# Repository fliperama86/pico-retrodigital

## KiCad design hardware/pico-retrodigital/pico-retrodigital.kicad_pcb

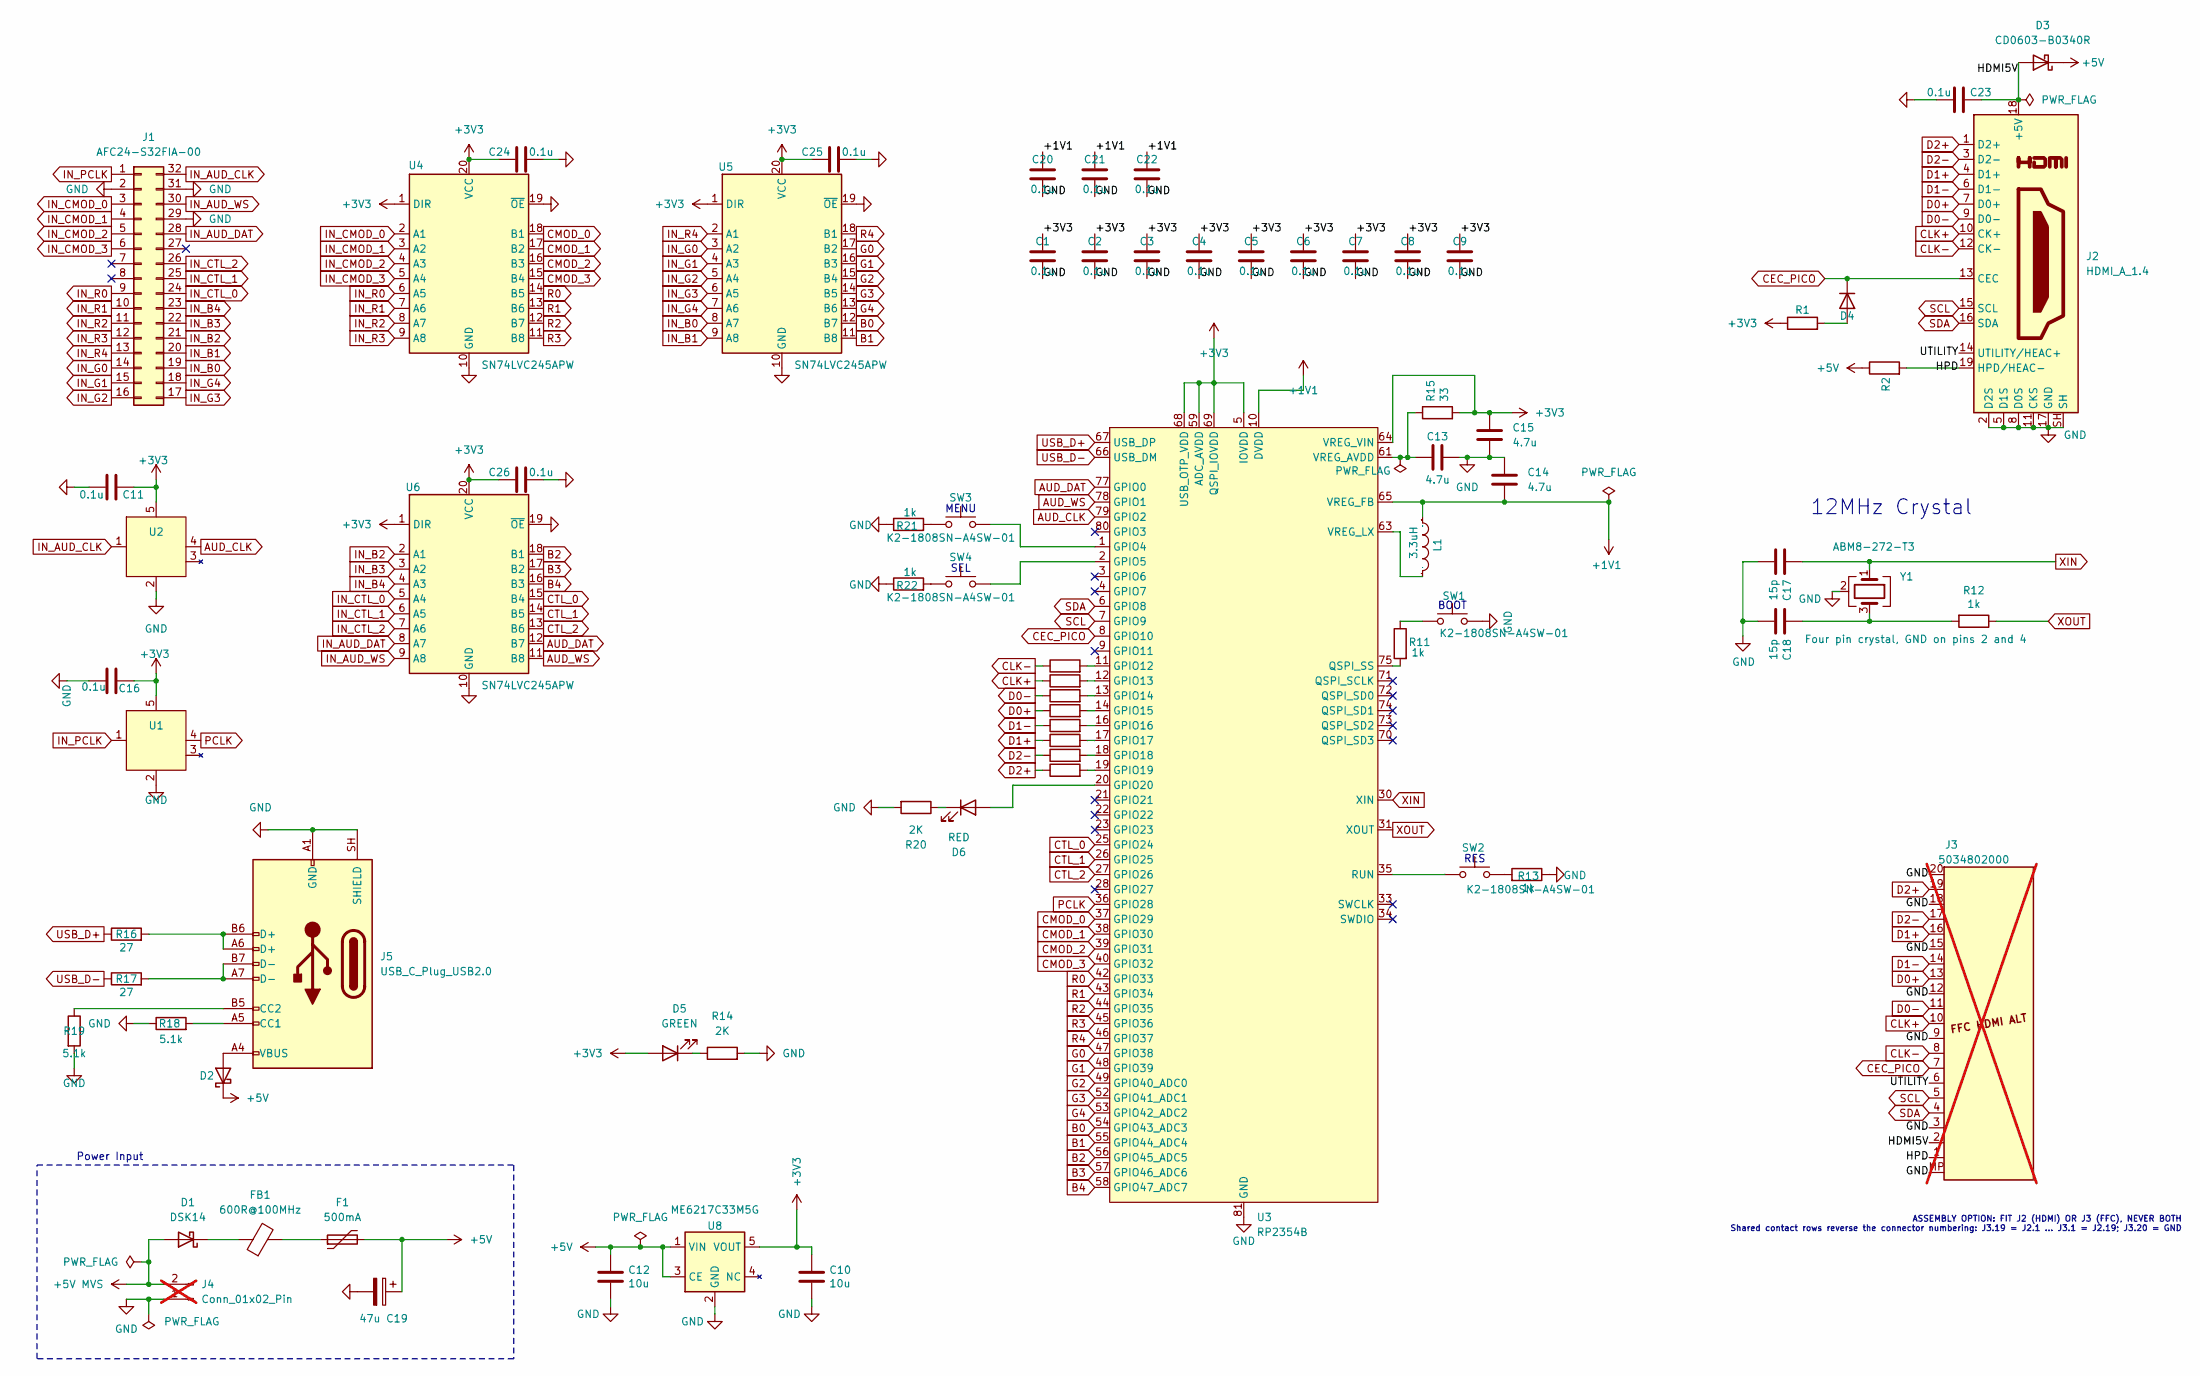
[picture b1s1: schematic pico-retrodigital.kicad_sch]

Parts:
C1, C3, C4, C5, C6, C7, C8, C9, C11, C16, C20, C21, C22, C23, C24, C25, C26: 0.1u; C_0402_1005Metric; LCSC C1525
C2: 0.1u; C_0603_1608Metric; LCSC C14663
C10, C12: 10u; C_0402_1005Metric; LCSC C15525
C13, C15: 4.7u; C_0402_1005Metric; LCSC C23733
C14: 4.7u; C_0603_1608Metric; LCSC C19666
C17, C18: 15p; C_0402_1005Metric; LCSC C1548
C19: 47u; C_1206_3216Metric; MPN CL31A476MPHNNNE; LCSC C96123
D1: DSK14; D_SOD-123; LCSC C7502711
D2: DSK14; D_SOD-123; MPN DSK14; LCSC C7502711
D3, D4: CD0603-B0340R; D_0603_1608Metric; MPN CD0603-B0340R; LCSC C3759853
D5: GREEN; LED_0603_1608Metric; MPN KT-0603YG; LCSC C2289
D6: RED; LED_0603_1608Metric; MPN KT-0603R; LCSC C2286
F1: 500mA; C_0603_1608Metric; MPN BSMD0603-050-6V; LCSC C883095
FB1: 600R@100MHz; C_0603_1608Metric; MPN BLM18KG601SN1D; LCSC C85833
J1: AFC24-S32FIA-00; FPC-SMD_P0.50-32P_JS_AFC24-S32FIA-00; MPN AFC24-S32FIA-00; LCSC C2908587
J2: HDMI_A_1.4; HDMI_A_Molex_208658-1001_Horizontal; MPN HDMI-001 19PCBTP; LCSC C138388
J3: 5034802000; FPC-SMD_5034802000; MPN 5034802000; LCSC C234192; not fitted
J4: Conn_01x02_Pin; JST_XA_B02B-XASK-1_1x02_P2.50mm_Vertical; MPN B02B-XASK-1(LF)(SN); LCSC C263753; not fitted
J5: USB_C_Plug_USB2.0; USB_C_Receptacle_HRO_TYPE-C-31-M-12; MPN TYPE-C-31-M-12; LCSC C165948
L1: IND-SMD_L2.0-W1.6_AOTA-B201610S3R3-101-T; Manufacturer Part AOTA-B201610S3R3-101-T; LCSC Part Name AOTA-B201610S3R3-101-T
R1: 27K; R_0402_1005Metric; LCSC C25771
R2: 10K; R_0603_1608Metric; LCSC C25804
R3, R4, R5, R6, R7, R8, R9, R10: 220; R_0402_1005Metric; LCSC C25091
R11, R12, R13, R21, R22: 1k; R_0402_1005Metric; LCSC C11702
R14, R20: 2K; R_0402_1005Metric; LCSC C4109
R15: 33; R_0402_1005Metric; LCSC C25105
R16, R17: 27; R_0603_1608Metric; LCSC C25190
R18, R19: 5.1k; R_0603_1608Metric; LCSC C23186
SW1, SW2, SW3, SW4: K2-1808SN-A4SW-01; SW_Push_1P1T_NO_Vertical_Wuerth_434133025816; LCSC C92589
U1, U2: SN74LVC1G17DBVR; SOT-23-5; LCSC C7836
U3: RP2354B; QFN-80-1EP_10x10mm_P0.4mm_EP3.4x3.4mm_ThermalVias; LCSC C39843328
U4, U5, U6: SN74LVC245APW; TSSOP-20_4.4x6.5mm_P0.65mm; LCSC C7848
U8: ME6217C33M5G; SOT-23-5; LCSC C427602
Y1: ABM8-272-T3; Crystal_SMD_3225-4Pin_3.2x2.5mm; LCSC C20625731

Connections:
+1V1: C14.2, C20.1, C21.1, C22.1, L1.1, U3.10 (DVDD), U3.32 (DVDD), U3.51 (DVDD), U3.65 (VREG_FB)
+3V3: C1.1, C2.1, C3.1, C4.1, C5.1, C6.1, C7.1, C8.1, C9.1, C10.1, C11.1, C15.1, C16.1, C24.1, C25.1, C26.1, D5.2 (A), R1.1, R15.2, U1.5 (VCC), U2.5 (VCC), U3.5 (IOVDD), U3.15 (IOVDD), U3.24 (IOVDD), U3.29 (IOVDD), U3.41 (IOVDD), U3.50 (IOVDD), U3.59 (ADC_AVDD), U3.60 (IOVDD), U3.64 (VREG_VIN), U3.68 (USB_OTP_VDD), U3.69 (QSPI_IOVDD), U3.76 (IOVDD), U4.1 (DIR), U4.20 (VCC), U5.1 (DIR), U5.20 (VCC), U6.1 (DIR), U6.20 (VCC), U8.5 (VOUT)
+5V: C12.1, C19.1, D2.1 (K), D3.1 (K), F1.2, R2.1, U8.1 (VIN), U8.3 (CE)
+5V MVS: D1.2 (A), J4.2
/HDMI5V: C23.1, D3.2 (A), J2.18 (+5V), J3.2 (+5V)
/HPD: J2.19 (HPD/HEAC-), J3.1 (HPD), R2.2
/UTILITY: J2.14 (UTILITY/HEAC+), J3.6 (UTILITY)
AUD_CLK: U2.4 (Y), U3.79 (GPIO2)
AUD_DAT: U3.77 (GPIO0), U6.12 (B7)
AUD_WS: U3.78 (GPIO1), U6.11 (B8)
B0: U3.54 (GPIO43_ADC3), U5.12 (B7)
B1: U3.55 (GPIO44_ADC4), U5.11 (B8)
B2: U3.56 (GPIO45_ADC5), U6.18 (B1)
B3: U3.57 (GPIO46_ADC6), U6.17 (B2)
B4: U3.58 (GPIO47_ADC7), U6.16 (B3)
CEC_PICO: D4.1 (K), J2.13 (CEC), J3.7 (CEC), U3.8 (GPIO10)
CLK+: J2.10 (CK+), J3.10 (CLK+), R5.1
CLK-: J2.12 (CK-), J3.8 (CLK-), R4.1
CMOD_0: U3.37 (GPIO29), U4.18 (B1)
CMOD_1: U3.38 (GPIO30), U4.17 (B2)
CMOD_2: U3.39 (GPIO31), U4.16 (B3)
CMOD_3: U3.40 (GPIO32), U4.15 (B4)
CTL_0: U3.25 (GPIO24), U6.15 (B4)
CTL_1: U3.26 (GPIO25), U6.14 (B5)
CTL_2: U3.27 (GPIO26), U6.13 (B6)
D0+: J2.7 (D0+), J3.13 (D0+), R6.1
D0-: J2.9 (D0-), J3.11 (D0-), R3.1
D1+: J2.4 (D1+), J3.16 (D1+), R8.1
D1-: J2.6 (D1-), J3.14 (D1-), R7.1
D2+: J2.1 (D2+), J3.19 (D2+), R10.1
D2-: J2.3 (D2-), J3.17 (D2-), R9.1
G0: U3.47 (GPIO38), U5.17 (B2)
G1: U3.48 (GPIO39), U5.16 (B3)
G2: U3.49 (GPIO40_ADC0), U5.15 (B4)
G3: U3.52 (GPIO41_ADC1), U5.14 (B5)
G4: U3.53 (GPIO42_ADC2), U5.13 (B6)
GND: C1.2, C2.2, C3.2, C4.2, C5.2, C6.2, C7.2, C8.2, C9.2, C10.2, C11.2, C12.2, C13.2, C14.1, C15.2, C16.2, C17.2, C18.2, C19.2, C20.2, C21.2, C22.2, C23.2, C24.2, C25.2, C26.2, J1.2, J1.29, J1.31, J2.2 (D2S), J2.5 (D1S), J2.8 (D0S), J2.11 (CKS), J2.17 (GND), J2.SH, J3.3 (GND), J3.9 (GND), J3.12 (GND), J3.15 (GND), J3.18 (GND), J3.20 (GND), J3.MP (SHIELD), J4.1, J5.A1 (GND), J5.A12 (GND), J5.B1 (GND), J5.B12 (GND), J5.SH (SHIELD), R13.1, R14.2, R18.1, R19.2, R20.2, R21.1, R22.1, SW1.1, U1.2 (GND), U2.2 (GND), U3.62 (VREG_PGND), U3.81 (GND), U4.10 (GND), U4.19 (~OE), U5.10 (GND), U5.19 (~OE), U6.10 (GND), U6.19 (~OE), U8.2 (GND), Y1.2 (G), Y1.4 (G)
IN_AUD_CLK: J1.32, U2.1 (A)
IN_AUD_DAT: J1.28, U6.8 (A7)
IN_AUD_WS: J1.30, U6.9 (A8)
IN_B0: J1.19, U5.8 (A7)
IN_B1: J1.20, U5.9 (A8)
IN_B2: J1.21, U6.2 (A1)
IN_B3: J1.22, U6.3 (A2)
IN_B4: J1.23, U6.4 (A3)
IN_CMOD_0: J1.3, U4.2 (A1)
IN_CMOD_1: J1.4, U4.3 (A2)
IN_CMOD_2: J1.5, U4.4 (A3)
IN_CMOD_3: J1.6, U4.5 (A4)
IN_CTL_0: J1.24, U6.5 (A4)
IN_CTL_1: J1.25, U6.6 (A5)
IN_CTL_2: J1.26, U6.7 (A6)
IN_G0: J1.14, U5.3 (A2)
IN_G1: J1.15, U5.4 (A3)
IN_G2: J1.16, U5.5 (A4)
IN_G3: J1.17, U5.6 (A5)
IN_G4: J1.18, U5.7 (A6)
IN_PCLK: J1.1, U1.1 (A)
IN_R0: J1.9, U4.6 (A5)
IN_R1: J1.10, U4.7 (A6)
IN_R2: J1.11, U4.8 (A7)
IN_R3: J1.12, U4.9 (A8)
IN_R4: J1.13, U5.2 (A1)
unnamed: C18.1, R12.2, Y1.3
unnamed: D1.1 (K), FB1.1
unnamed: D2.2 (A), J5.A4 (VBUS), J5.A9 (VBUS), J5.B4 (VBUS), J5.B9 (VBUS)
unnamed: D4.2 (A), R1.2
unnamed: D5.1 (K), R14.1
unnamed: D6.2 (A), U3.20 (GPIO20)
unnamed: D6.1 (K), R20.1
unnamed: F1.1, FB1.2
unnamed: J5.A5 (CC1), R18.2
unnamed: J5.B5 (CC2), R19.1
unnamed: J5.A6 (D+), J5.B6 (D+), R16.2
unnamed: J5.A7 (D-), J5.B7 (D-), R17.2
unnamed: R11.1, SW1.2
unnamed: R13.2, SW2.1
unnamed: R21.2, SW3.1
unnamed: R22.2, SW4.1
unnamed: SW3.2, U3.1 (GPIO4)
unnamed: SW4.2, U3.2 (GPIO5)
unnamed: R4.2, U3.11 (GPIO12)
unnamed: R5.2, U3.12 (GPIO13)
unnamed: R3.2, U3.13 (GPIO14)
unnamed: R6.2, U3.14 (GPIO15)
unnamed: R7.2, U3.16 (GPIO16)
unnamed: R8.2, U3.17 (GPIO17)
unnamed: R9.2, U3.18 (GPIO18)
unnamed: R10.2, U3.19 (GPIO19)
unnamed: R11.2, U3.75 (QSPI_SS)
unnamed: SW2.2, U3.35 (RUN)
unnamed: C13.1, R15.1, U3.61 (VREG_AVDD)
unnamed: L1.2, U3.63 (VREG_LX)
PCLK: U1.4 (Y), U3.36 (GPIO28)
R0: U3.42 (GPIO33), U4.14 (B5)
R1: U3.43 (GPIO34), U4.13 (B6)
R2: U3.44 (GPIO35), U4.12 (B7)
R3: U3.45 (GPIO36), U4.11 (B8)
R4: U3.46 (GPIO37), U5.18 (B1)
SCL: J2.15 (SCL), J3.5 (SCL), U3.7 (GPIO9)
SDA: J2.16 (SDA), J3.4 (SDA), U3.6 (GPIO8)
USB_D+: R16.1, U3.67 (USB_DP)
USB_D-: R17.1, U3.66 (USB_DM)
XIN: C17.1, U3.30 (XIN), Y1.1
XOUT: R12.1, U3.31 (XOUT)

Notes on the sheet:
Power Input
12MHz Crystal
SEL
ASSEMBLY OPTION: FIT J2 (HDMI) OR J3 (FFC), NEVER BOTH Shared contact rows reverse the connector numbering: J3.19 = J2.1 ... J3.1 = J2.19; J3.20 = GND
MENU
RES
BOOT

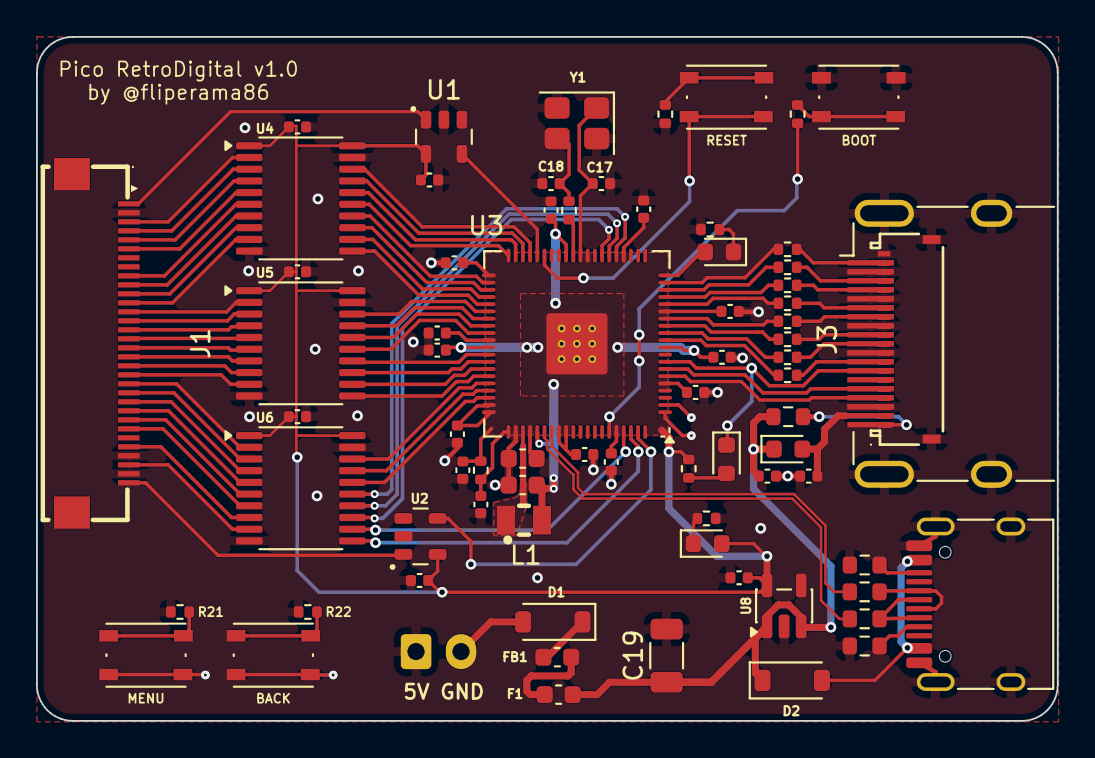
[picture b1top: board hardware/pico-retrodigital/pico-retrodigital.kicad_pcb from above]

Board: 4 copper layers, 56.7 x 38.0 mm, 74 parts (0 on the bottom side), 105 nets.

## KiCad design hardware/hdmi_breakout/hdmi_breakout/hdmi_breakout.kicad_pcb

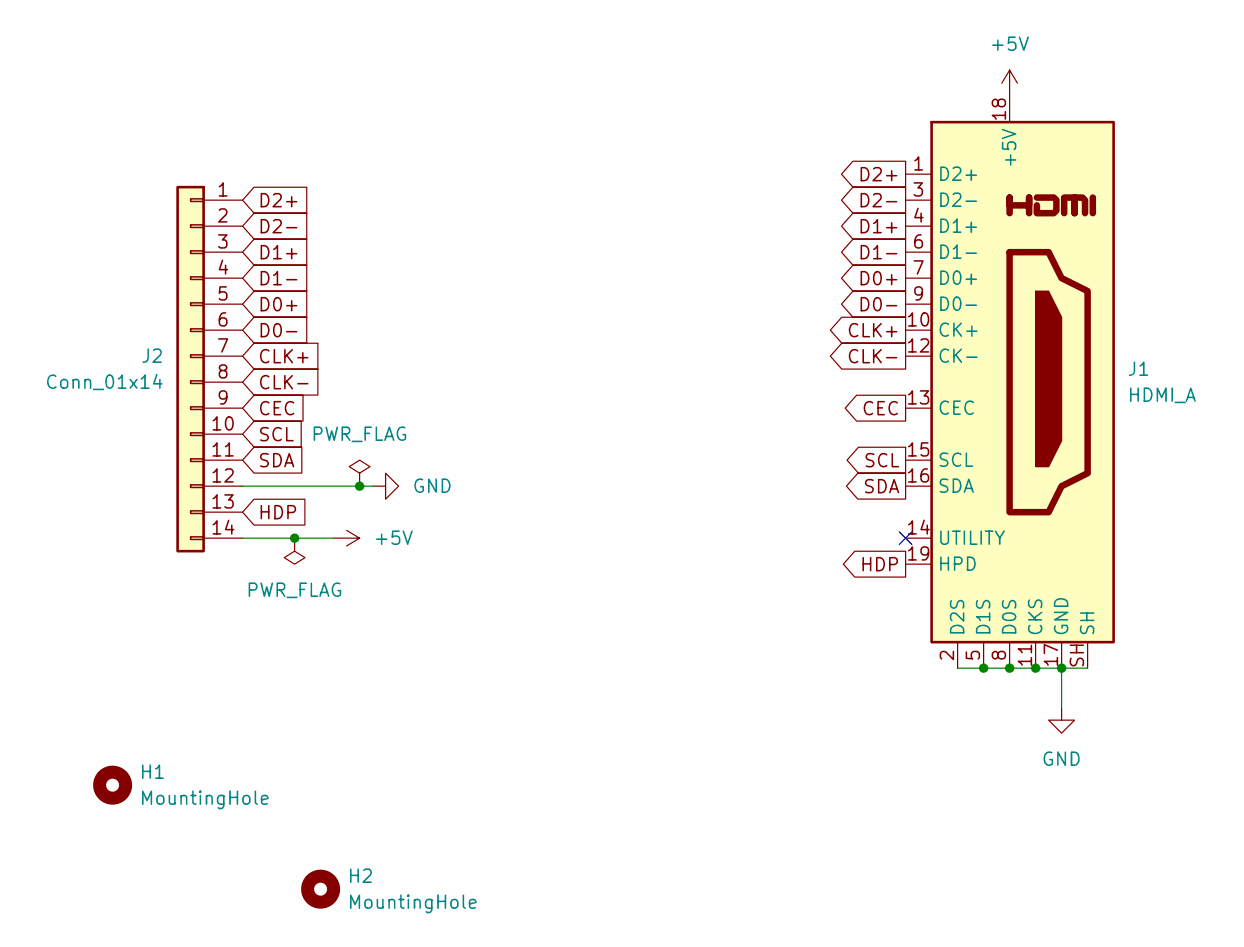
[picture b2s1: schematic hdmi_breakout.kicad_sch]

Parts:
H1, H2: MountingHole; MountingHole_3mm
J1: HDMI_A; HDMI_A_Molex_208658-1001_Horizontal
J2: Conn_01x14; TE_1-1734839-4_1x14-1MP_P0.5mm_Horizontal

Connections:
+5V: J1.18 (+5V), J2.14
CEC: J1.13 (CEC), J2.9
CLK+: J1.10 (CK+), J2.7
CLK-: J1.12 (CK-), J2.8
D0+: J1.7 (D0+), J2.5
D0-: J1.9 (D0-), J2.6
D1+: J1.4 (D1+), J2.3
D1-: J1.6 (D1-), J2.4
D2+: J1.1 (D2+), J2.1
D2-: J1.3 (D2-), J2.2
GND: J1.2 (D2S), J1.5 (D1S), J1.8 (D0S), J1.11 (CKS), J1.17 (GND), J1.SH, J2.12
HDP: J1.19 (HPD), J2.13
SCL: J1.15 (SCL), J2.10
SDA: J1.16 (SDA), J2.11

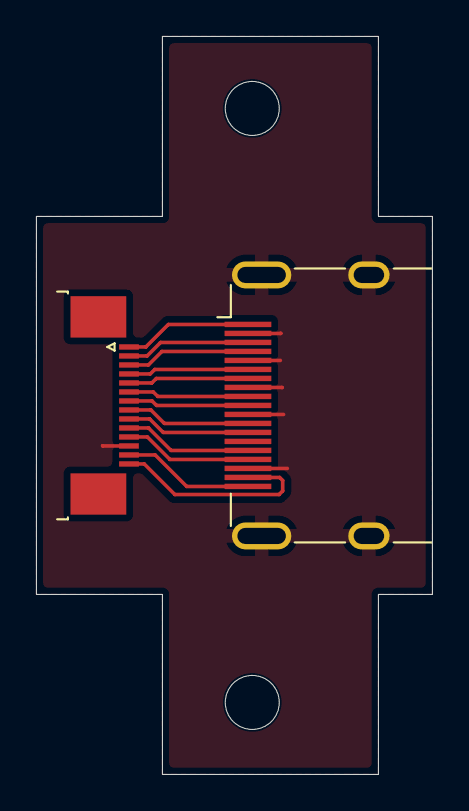
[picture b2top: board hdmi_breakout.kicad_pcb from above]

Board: 2 copper layers, 22.0 x 41.0 mm, 4 parts (0 on the bottom side), 14 nets.

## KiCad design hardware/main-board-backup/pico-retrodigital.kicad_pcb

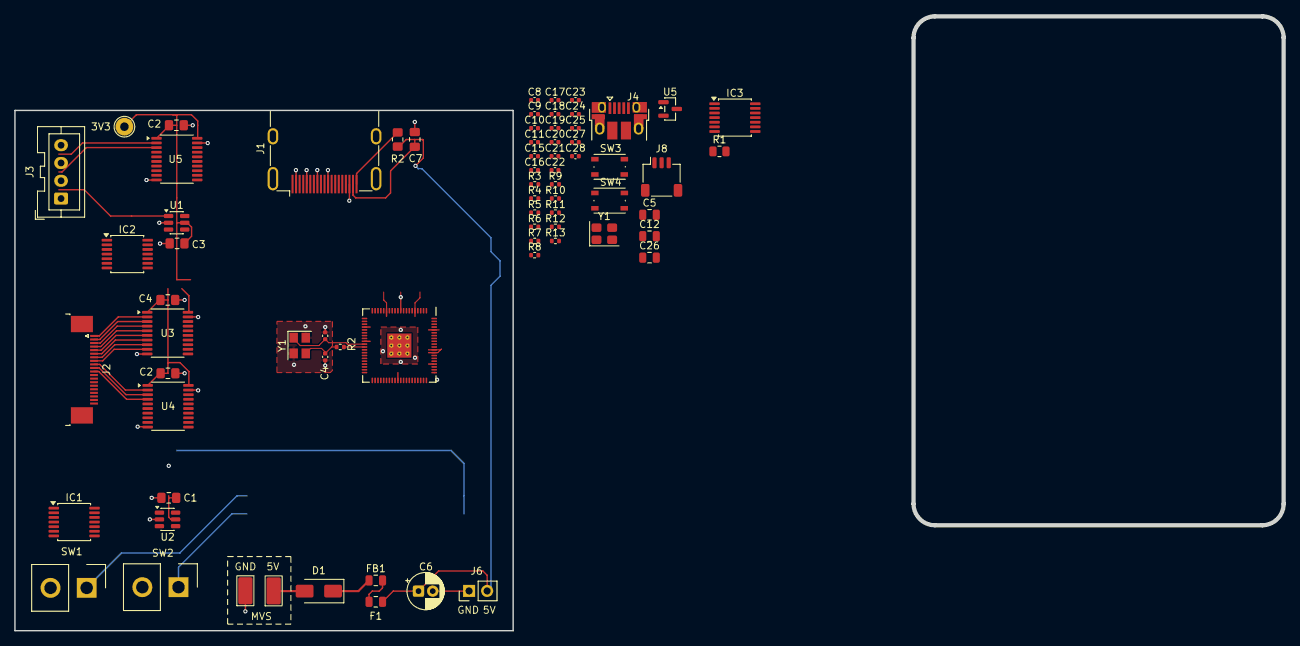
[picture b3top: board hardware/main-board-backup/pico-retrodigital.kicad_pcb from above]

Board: 2 copper layers, 178.3 x 86.3 mm, 69 parts (0 on the bottom side), 46 nets.

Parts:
3V3: TestPoint_THTPad_D2.5mm_Drill1.2mm
C1, C2, C2#2, C3#2, C4#2, C7: 0.1u; C_0805_2012Metric_Pad1.18x1.45mm_HandSolder
C3, C4, C10, C11: 15p; C_0402_1005Metric
C5, C12, C26: 10u; C_0805_2012Metric
C6: 47u; CP_Radial_D5.0mm_P2.00mm
C8, C15, C18, C19, C20, C21, C22, C23, C24, C25, C27, C28: 100n; C_0402_1005Metric
C9: DNF; C_0402_1005Metric
C16, C17: 4.7u; C_0402_1005Metric
D1: SS14; D_SMA
F1: Polyfuse; C_0805_2012Metric
FB1: FerriteBead; C_0805_2012Metric
IC1, IC2, IC3: TXU0104PWR; TSSOP-14_4.4x5mm_P0.65mm
J1: HDMI_A; HDMI_A_Molex_208658-1001_Horizontal
J2: Conn_02x05_Top_Bottom; TE_2-1734839-0_1x20-1MP_P0.5mm_Horizontal
J3: Conn_01x04; JST_XA_B04B-XASK-1_1x04_P2.50mm_Vertical
J4: USB_B_Micro; USB_Micro-B_Amphenol_10103594-0001LF_Horizontal
J6: Conn_01x02_Pin; PinHeader_1x02_P2.54mm_Vertical
J8: SM03B-SRSS-TB; JST_SH_SM03B-SRSS-TB_1x03-1MP_P1.00mm_Horizontal
R1: 27K; R_0805_2012Metric
R2, R8, R9, R11: 1k; R_0402_1005Metric
R2#2: 10K; R_0805_2012Metric_Pad1.20x1.40mm_HandSolder
R3, R5, R6, R7: DNF; R_0402_1005Metric
R4: 0; R_0402_1005Metric
R10: 33; R_0402_1005Metric
R12, R13: 27; R_0402_1005Metric
SW1: MENU; Samtec_HPM-02-01-x-S_Straight_1x02_Pitch5.08mm
SW2: BACK; Samtec_HPM-02-01-x-S_Straight_1x02_Pitch5.08mm
SW3, SW4: SW_Push; SW_Push_1P1T_NO_Vertical_Wuerth_434133025816
U1: RP2350_80QFN; RP2350-QFN-80-1EP_10x10_P0.4mm_EP3.4x3.4mm_ThermalVias
U1#2: A_BUFF; SOT-23-6
U2: V_BUFF; SOT-23-6
U3: RG_LVS; TSSOP-20_4.4x6.5mm_P0.65mm
U4: GB_LVS; TSSOP-20_4.4x6.5mm_P0.65mm
U5: AP2127K-3.3TRG1; SOT-23
U5#2: AV_LVS; TSSOP-20_4.4x6.5mm_P0.65mm
Y1, Y1#2: ABM8-272-T3; Crystal_SMD_3225-4Pin_3.2x2.5mm

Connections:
+1V1: C15.1, C17.1, C18.1, U1.10 (DVDD), U1.32 (DVDD), U1.51 (DVDD), U1.65 (VREG_FB)
+3V3: 3V3.1, C1.1, C2.1, C2#2.1, C3#2.1, C4#2.1, C8.1, C9.1, C12.1, C19.1, C20.1, C21.1, C22.1, C23.1, C24.1, C25.1, C26.1, C27.1, C28.1, IC1.8 (OE), IC1.14 (VCCB), IC2.8 (OE), IC2.14 (VCCB), R1.1, R6.1, R7.1, R10.1, U1.5 (IOVDD), U1.15 (IOVDD), U1.24 (IOVDD), U1.29 (IOVDD), U1.41 (IOVDD), U1.50 (IOVDD), U1.59 (ADC_AVDD), U1.60 (IOVDD), U1.64 (VREG_VIN), U1.68 (USB_OTP_VDD), U1.69 (QSPI_IOVDD), U1.76 (IOVDD), U1#2.5 (V_{CC}), U2.5 (V_{CC}), U3.1 (DIR), U3.20 (VCC), U4.1 (DIR), U4.20 (VCC), U5#2.1 (DIR), U5#2.20 (VCC)
+5V: C6.1, C7.1, F1.2, IC1.1 (VCCA), IC2.1 (VCCA), J1.18 (+5V), J6.2, R2#2.1
/RP2350B/FLASH2_SS: R5.2, R7.2
/RP2350B/FLASH_SS: R3.2, R4.2, R6.2
/RP2350B/GPIO0: R3.1, R5.1
/RP2350B/QSPI_SS: R4.1, R11.1
/RP2350B/USB_D+: J4.3 (D+), R12.1
/RP2350B/USB_D-: J4.2 (D-), R13.1
/RP2350B/VREG_AVDD: C16.1, R10.2
/RP2350B/XIN: C10.1, Y1.1
/RP2350B/~USB_BOOT: R11.2, SW3.2
/XIN: C3.1, U1.30 (XIN), Y1#2.1
/XOUT: R2.1, U1.31 (XOUT)
CEC_PICO: J1.13 (CEC), R1.2
GND: C1.2, C2.2, C2#2.2, C3.2, C3#2.2, C4.2, C4#2.2, C5.2, C6.2, C7.2, C8.2, C9.2, C10.2, C11.2, C12.2, C15.2, C16.2, C17.2, C18.2, C19.2, C20.2, C21.2, C22.2, C23.2, C24.2, C25.2, C26.2, C27.2, C28.2, IC1.7 (GND), IC2.7 (GND), J1.2 (D2S), J1.5 (D1S), J1.8 (D0S), J1.11 (CKS), J1.17 (GND), J1.SH, J4.5 (GND), J4.6 (Shield), J6.1, J8.2, J8.MP (MountPin), R8.2, SW1.2, SW2.2, SW3.1, U1.62 (VREG_PGND), U1.81 (GND), U1#2.2 (GND), U2.2 (GND), U3.10 (GND), U3.19 (~OE), U4.10 (GND), U4.19 (~OE), U5.2 (GND), U5#2.10 (GND), U5#2.19 (~OE), Y1.2, Y1.4, Y1#2.2, Y1#2.4
IN_A1: IC2.3 (A2), J3.2
IN_A2: IC2.4 (A3), J3.3
IN_A3: IC2.5 (A4), J3.4
IN_ACLK: IC2.2 (A1), J3.1
IN_B0: J2.11, U4.4 (A3)
IN_B1: J2.12, U4.5 (A4)
IN_B2: J2.13, U4.6 (A5)
IN_B3: J2.14, U4.7 (A6)
IN_B4: J2.15, U4.8 (A7)
IN_C1: IC1.3 (A2), J2.16
IN_C2: IC1.4 (A3), J2.17
IN_C3: IC1.5 (A4), J2.18
IN_G0: J2.6, U3.7 (A6)
IN_G1: J2.7, U3.8 (A7)
IN_G2: J2.8, U3.9 (A8)
IN_G3: J2.9, U4.2 (A1)
IN_G4: J2.10, U4.3 (A2)
IN_PCLK: IC1.2 (A1), J2.19
IN_R0: J2.1, U3.2 (A1)
IN_R1: J2.2, U3.3 (A2)
IN_R2: J2.3, U3.4 (A3)
IN_R3: J2.4, U3.5 (A4)
IN_R4: J2.5, U3.6 (A5)
unnamed: C4.1, R2.2, Y1#2.3
unnamed: C11.1, R9.2, Y1.3
unnamed: D1.1 (K), FB1.1
unnamed: F1.1, FB1.2
unnamed: J1.19 (HPD), R2#2.2
unnamed: R8.1, SW4.1
VBUS: C5.1, J4.1 (VBUS), U5.1 (VIN)

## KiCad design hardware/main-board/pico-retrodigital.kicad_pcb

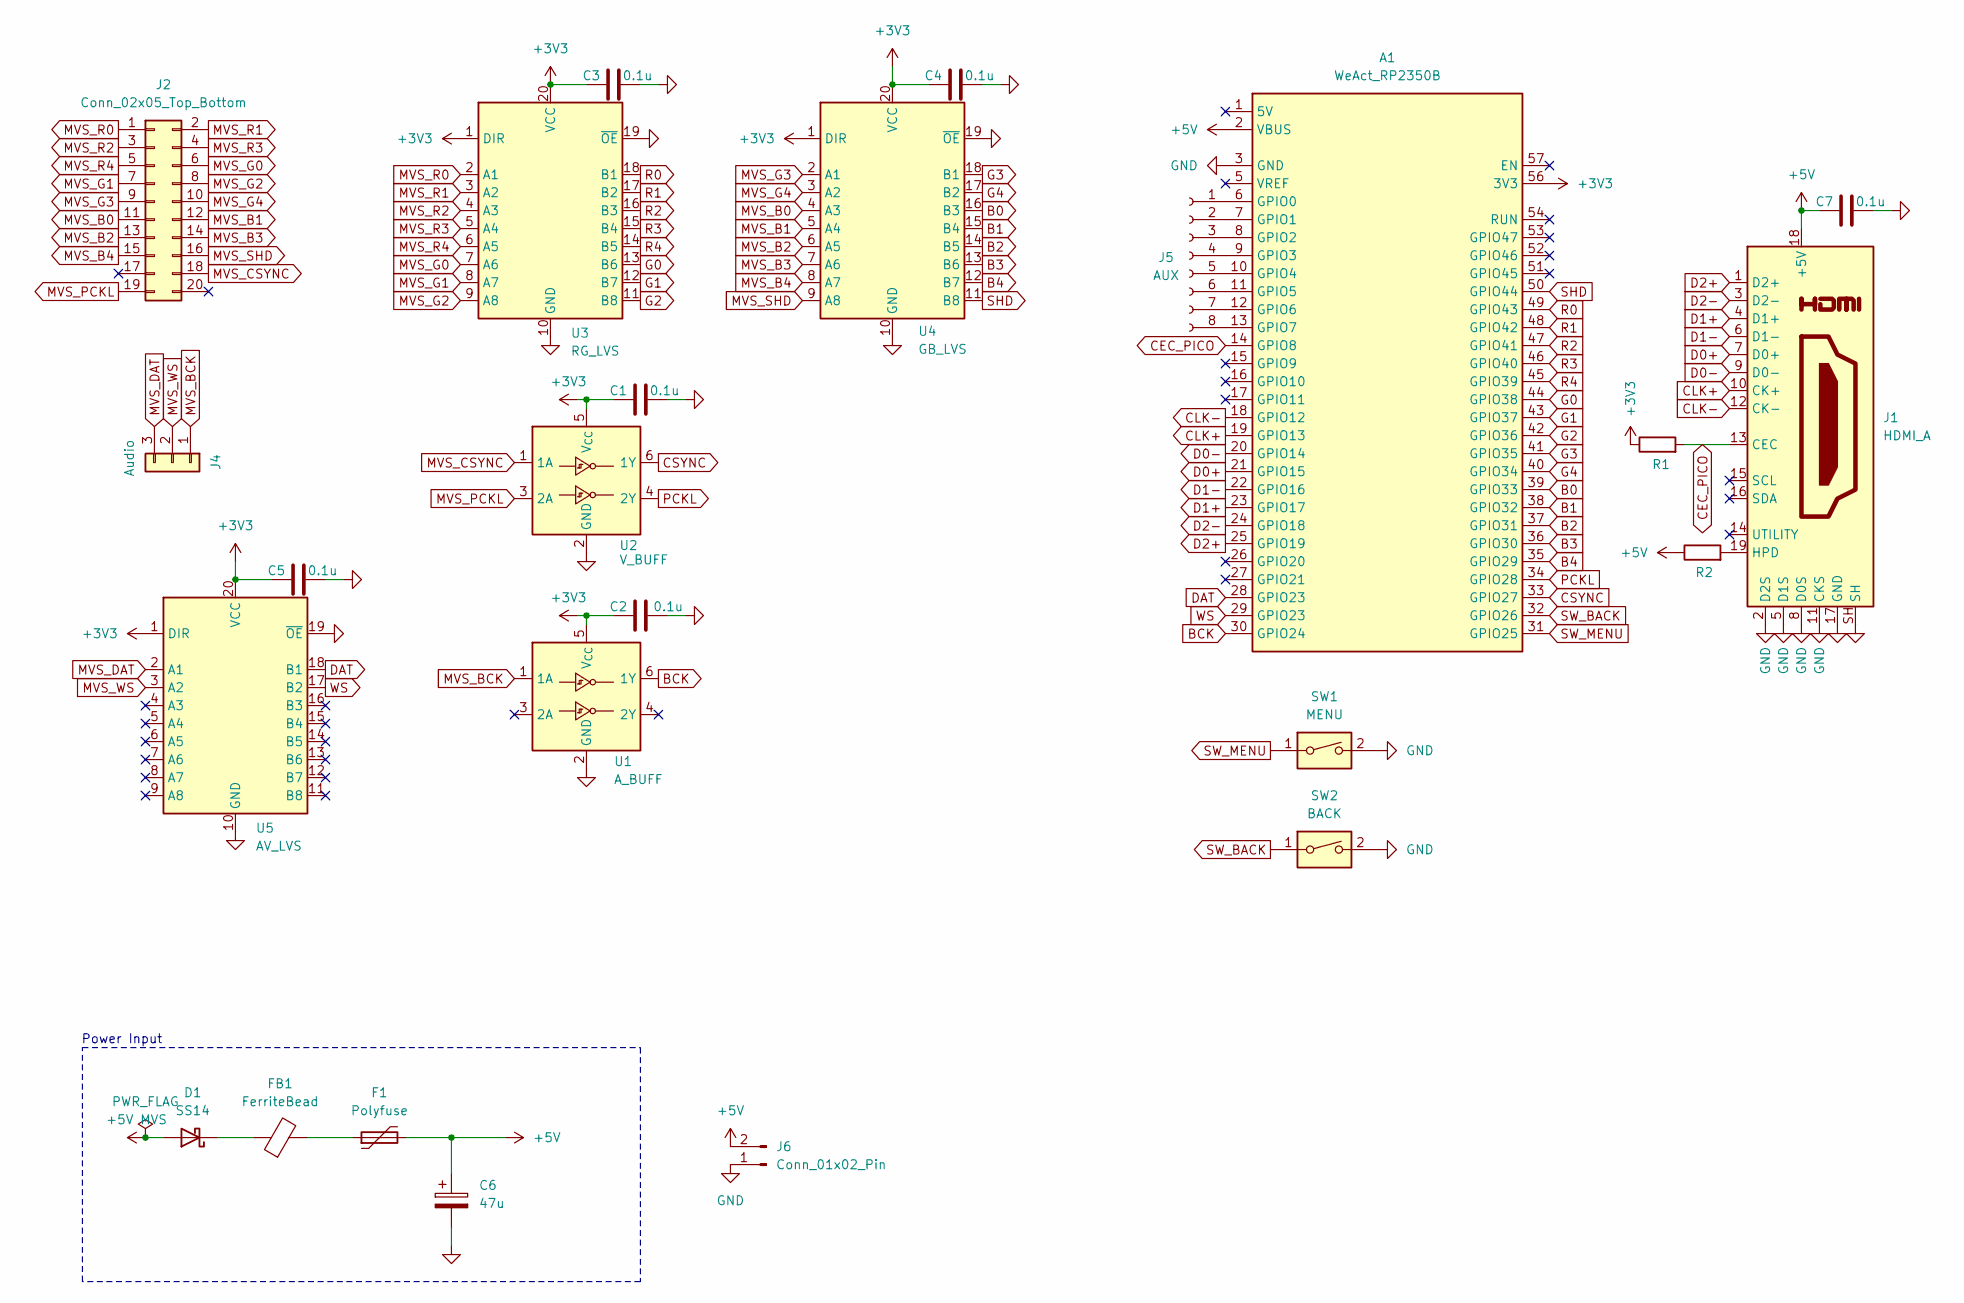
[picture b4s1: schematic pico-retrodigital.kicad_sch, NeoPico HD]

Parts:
A1: WeAct_RP2350B
C1, C2, C3, C4, C5, C7: 0.1u; C_0805_2012Metric_Pad1.18x1.45mm_HandSolder
C6: 47u; CP_Radial_D5.0mm_P2.00mm
D1: SS14; D_SMA
F1: Polyfuse; C_0805_2012Metric
FB1: FerriteBead; C_0805_2012Metric
J1: HDMI_A; HDMI_A_Molex_208658-1001_Horizontal
J2: Conn_02x05_Top_Bottom; IDC-Header_2x10_P2.54mm_Vertical
J4: Audio; JST_XA_B03B-XASK-1_1x03_P2.50mm_Vertical
J5: AUX; PinHeader_2x04_P2.54mm_Vertical
J6: Conn_01x02_Pin; PinHeader_1x02_P2.54mm_Vertical
R1: 27K; R_0805_2012Metric
R2: 10K; R_0805_2012Metric_Pad1.20x1.40mm_HandSolder
SW1: MENU; Samtec_HPM-02-01-x-S_Straight_1x02_Pitch5.08mm
SW2: BACK; Samtec_HPM-02-01-x-S_Straight_1x02_Pitch5.08mm
U1: A_BUFF; SOT-23-6
U2: V_BUFF; SOT-23-6
U3: RG_LVS; TSSOP-20_4.4x6.5mm_P0.65mm
U4: GB_LVS; TSSOP-20_4.4x6.5mm_P0.65mm
U5: AV_LVS; TSSOP-20_4.4x6.5mm_P0.65mm

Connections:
+3V3: A1.55 (3V3), A1.56 (3V3), C1.1, C2.1, C3.1, C4.1, C5.1, R1.1, U1.5 (V_{CC}), U2.5 (V_{CC}), U3.1 (DIR), U3.20 (VCC), U4.1 (DIR), U4.20 (VCC), U5.1 (DIR), U5.20 (VCC); also elsewhere on the board
+5V: A1.2 (VBUS), C6.1, C7.1, F1.2, J1.18 (+5V), J6.2, R2.1
+5V MVS: D1.2 (A)
B0: A1.39 (GPIO33), U4.16 (B3)
B1: A1.38 (GPIO32), U4.15 (B4)
B2: A1.37 (GPIO31), U4.14 (B5)
B3: A1.36 (GPIO30), U4.13 (B6)
B4: A1.35 (GPIO29), U4.12 (B7)
BCK: A1.30 (GPIO24), U1.6 (1Y)
CEC_PICO: A1.14 (GPIO8), J1.13 (CEC), R1.2
CLK+: A1.19 (GPIO13), J1.10 (CK+)
CLK-: A1.18 (GPIO12), J1.12 (CK-)
CSYNC: A1.33 (GPIO27), U2.6 (1Y)
D0+: A1.21 (GPIO15), J1.7 (D0+)
D0-: A1.20 (GPIO14), J1.9 (D0-)
D1+: A1.23 (GPIO17), J1.4 (D1+)
D1-: A1.22 (GPIO16), J1.6 (D1-)
D2+: A1.25 (GPIO19), J1.1 (D2+)
D2-: A1.24 (GPIO18), J1.3 (D2-)
DAT: A1.28 (GPIO23), U5.18 (B1)
G0: A1.44 (GPIO38), U3.13 (B6)
G1: A1.43 (GPIO37), U3.12 (B7)
G2: A1.42 (GPIO36), U3.11 (B8)
G3: A1.41 (GPIO35), U4.18 (B1)
G4: A1.40 (GPIO34), U4.17 (B2)
GND: A1.3 (GND), A1.4 (GND), A1.58 (GND), A1.59 (GND), A1.60 (GND), C1.2, C2.2, C3.2, C4.2, C5.2, C6.2, C7.2, J1.2 (D2S), J1.5 (D1S), J1.8 (D0S), J1.11 (CKS), J1.17 (GND), J1.SH, J6.1, SW1.2, SW2.2, U1.2 (GND), U2.2 (GND), U3.10 (GND), U3.19 (~OE), U4.10 (GND), U4.19 (~OE), U5.10 (GND), U5.19 (~OE)
MVS_B0: J2.11, U4.4 (A3)
MVS_B1: J2.12, U4.5 (A4)
MVS_B2: J2.13, U4.6 (A5)
MVS_B3: J2.14, U4.7 (A6)
MVS_B4: J2.15, U4.8 (A7)
MVS_BCK: J4.1, U1.1 (1A)
MVS_CSYNC: J2.18, U2.1 (1A)
MVS_DAT: J4.3, U5.2 (A1)
MVS_G0: J2.6, U3.7 (A6)
MVS_G1: J2.7, U3.8 (A7)
MVS_G2: J2.8, U3.9 (A8)
MVS_G3: J2.9, U4.2 (A1)
MVS_G4: J2.10, U4.3 (A2)
MVS_PCKL: J2.19, U2.3 (2A)
MVS_R0: J2.1, U3.2 (A1)
MVS_R1: J2.2, U3.3 (A2)
MVS_R2: J2.3, U3.4 (A3)
MVS_R3: J2.4, U3.5 (A4)
MVS_R4: J2.5, U3.6 (A5)
MVS_SHD: J2.16, U4.9 (A8)
MVS_WS: J4.2, U5.3 (A2)
unnamed: A1.6 (GPIO0), J5.1
unnamed: A1.7 (GPIO1), J5.2
unnamed: A1.8 (GPIO2), J5.3
unnamed: A1.9 (GPIO3), J5.4
unnamed: A1.10 (GPIO4), J5.5
unnamed: A1.11 (GPIO5), J5.6
unnamed: A1.12 (GPIO6), J5.7
unnamed: A1.13 (GPIO7), J5.8
unnamed: D1.1 (K), FB1.1
unnamed: F1.1, FB1.2
unnamed: J1.19 (HPD), R2.2
PCKL: A1.34 (GPIO28), U2.4 (2Y)
R0: A1.49 (GPIO43), U3.18 (B1)
R1: A1.48 (GPIO42), U3.17 (B2)
R2: A1.47 (GPIO41), U3.16 (B3)
R3: A1.46 (GPIO40), U3.15 (B4)
R4: A1.45 (GPIO39), U3.14 (B5)
SHD: A1.50 (GPIO44), U4.11 (B8)
SW_BACK: A1.32 (GPIO26), SW2.1
SW_MENU: A1.31 (GPIO25), SW1.1
WS: A1.29 (GPIO23), U5.17 (B2)

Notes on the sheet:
Power Input

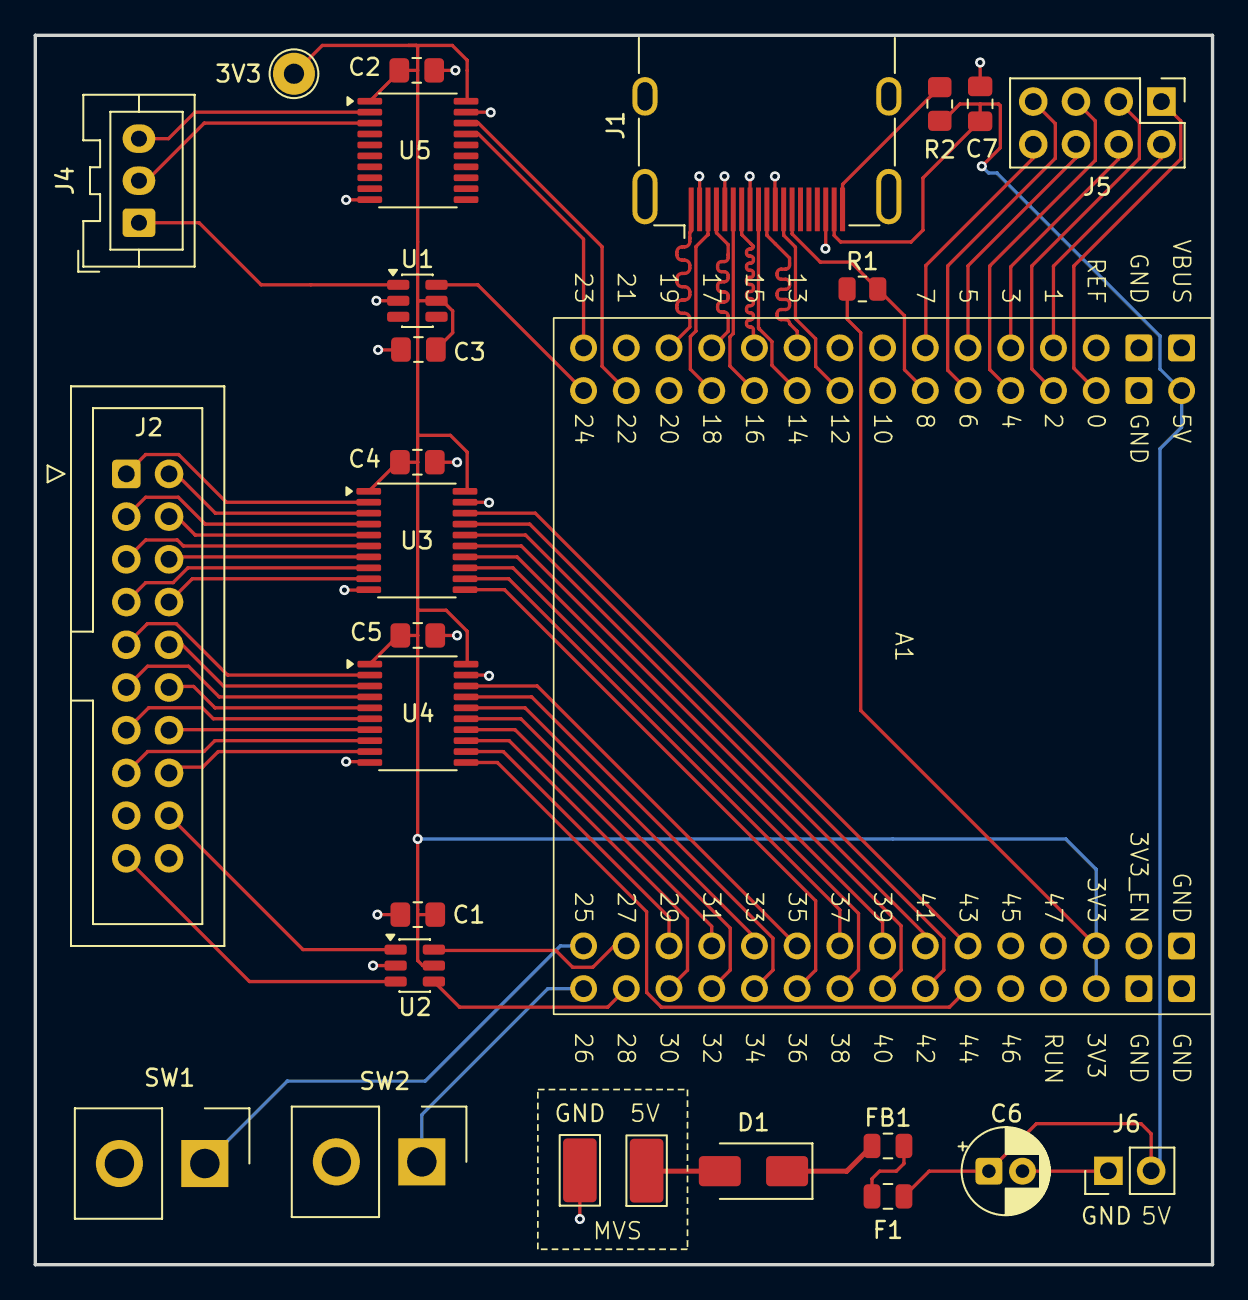
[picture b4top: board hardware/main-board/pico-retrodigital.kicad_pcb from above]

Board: 2 copper layers, 70.0 x 73.1 mm, 26 parts (0 on the bottom side), 67 nets.

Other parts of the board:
3V3: TestPoint_THTPad_D2.5mm_Drill1.2mm

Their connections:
+3V3: 3V3.1; also elsewhere on the board

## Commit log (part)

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2026-01-20 Copy kicad from neopico-hd
2026-04-26 USB C
2026-04-28 PCB fixes
2026-05-03 Square-shaped PCB
2026-05-14 Add 3V3 LDO regulator, reset/boot buttons, and pad default tweaks
    - Add ME6217C33M5G LDO symbol and integrate into schematic
    - Add RES1 (reset) and BOOT1 (boot) push buttons
    - Update default pad size in board setup
    - Ignore kicad-jlcpcb-tools plugin local state (jlcpcb/)
2026-05-14 Clean up PCB DRC: thermal reliefs, via drills, small-via rule
    - Bump all 0.6 mm vias to 0.3 mm drill (was 0.25); leave 9 small
    0.45/0.2 vias on +1V1 and CTL_0..2 untouched for tight routing
    - Update Default netclass via_drill to 0.3
    - Shrink thermal_bridge_width on both GND zones to 0.25 mm
    - Switch U3 GND (pads 62, 81) and +1V1 (pads 10, 32, 51, 65) to
    solid zone connection for better grounding/heat dissipation
2026-05-14 Refresh footprints from library; lower min silk text to 0.5 mm
    - Pull current library copies for standard 0402/0603 R, C, D and FFC
    connector footprints (clears 29 of 36 lib_footprint_mismatch warnings
    and the 2 silk_over_copper)
    - Drop min_text_height from 0.8 to 0.5 mm to match standard silk text
    on small SMD parts (clears 14 text_height warnings)
2026-05-14 Update PCB
2026-05-14 Add JLCPCB part numbers
